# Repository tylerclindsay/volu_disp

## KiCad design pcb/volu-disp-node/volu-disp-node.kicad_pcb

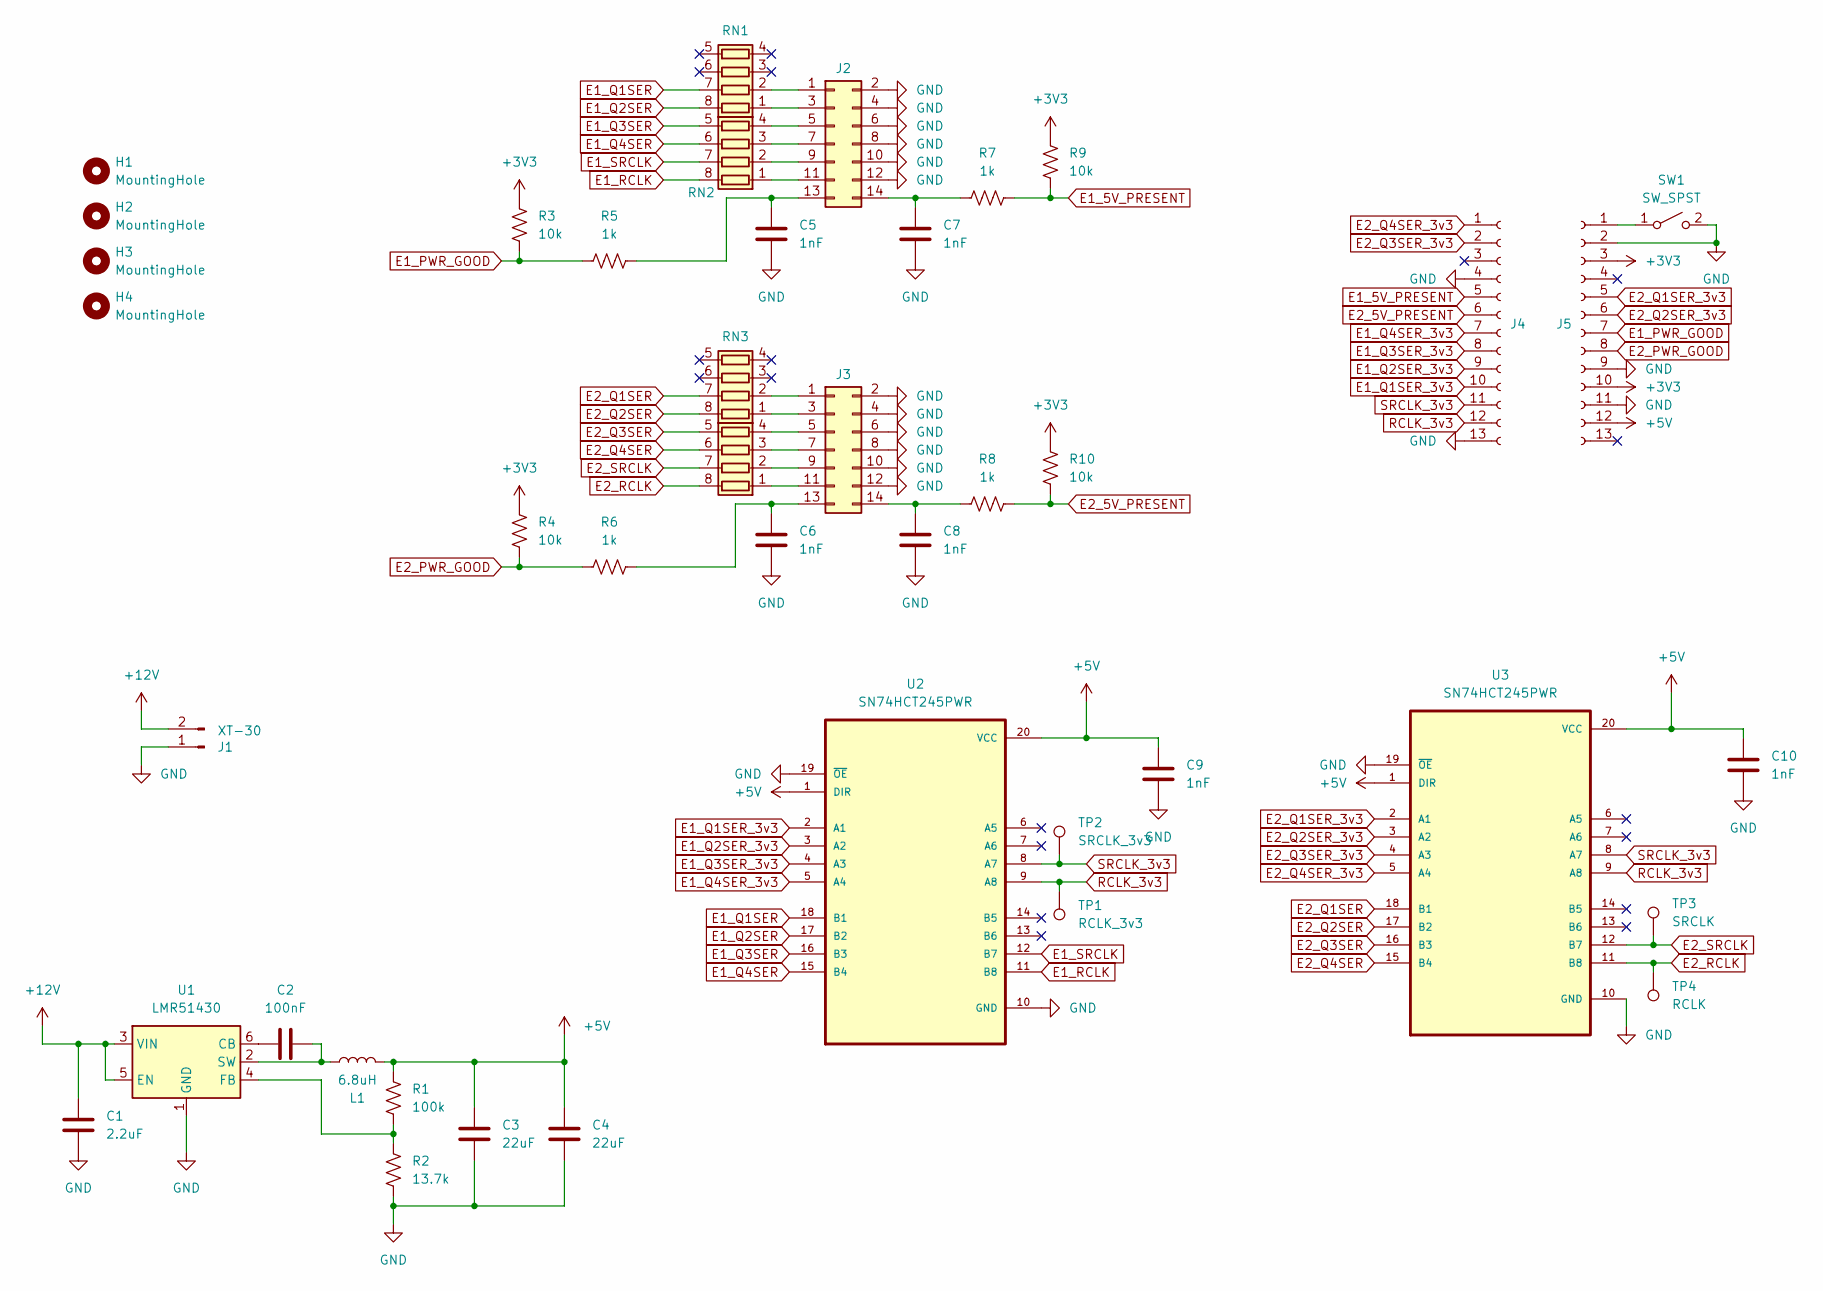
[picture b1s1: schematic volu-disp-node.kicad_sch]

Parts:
C1: 2.2uF; C_0603_1608Metric
C2: 100nF; C_0603_1608Metric
C3, C4: 22uF; C_0805_2012Metric
C5, C6, C7, C8, C9, C10: 1nF; C_0603_1608Metric
H1, H2, H3, H4: MountingHole; MountingHole_4.3mm_M4
J1: XT-30; AMASS_XT30PW-M_1x02_P2.50mm_Horizontal
J2, J3: Conn_02x07_Odd_Even; IDC-Header_2x07_P2.54mm_Latch_Vertical_SLIM
J4, J5: 01x13_Socket; PinSocket_1x13_P2.54mm_Vertical
L1: 6.8uH; L_7.3x7.3_H3.5
R1: 100k; R_0603_1608Metric
R2: 13.7k; R_0603_1608Metric
R3, R4, R9, R10: 10k; R_0603_1608Metric
R5, R6, R7, R8: 1k; R_0603_1608Metric
RN1, RN2, RN3, RN4: R_Pack04; R_Array_Convex_4x0603
SW1: SW_SPST; SW4_PTS815 SJM 250 SMTR LFS_CNK
TP1: RCLK_3v3; TestPoint_Pad_D2.0mm
TP2: SRCLK_3v3; TestPoint_Pad_D2.0mm
TP3: SRCLK; TestPoint_Pad_D2.0mm
TP4: RCLK; TestPoint_Pad_D2.0mm
U1: LMR51430; SOT-23-6
U2, U3: SN74HCT245PWR; SOP65P640X120-20N

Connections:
+3V3: J5.3, J5.10, R3.1, R4.1, R9.1, R10.1
+5V: C3.1, C4.1, C9.1, C10.1, J5.12, L1.2, R1.1, U2.1 (DIR), U2.20 (VCC), U3.1 (DIR), U3.20 (VCC)
+12V: C1.1, J1.2, U1.3 (VIN), U1.5 (EN)
E1_5V_PRESENT: J4.5, R7.2, R9.2
E1_PWR_GOOD: J5.7, R3.2, R5.1
E1_Q1SER: RN1.7 (R2.2), U2.18 (B1)
E1_Q1SER_3v3: J4.10, U2.2 (A1)
E1_Q2SER: RN1.8 (R1.2), U2.17 (B2)
E1_Q2SER_3v3: J4.9, U2.3 (A2)
E1_Q3SER: RN2.5 (R4.2), U2.16 (B3)
E1_Q3SER_3v3: J4.8, U2.4 (A3)
E1_Q4SER: RN2.6 (R3.2), U2.15 (B4)
E1_Q4SER_3v3: J4.7, U2.5 (A4)
E1_RCLK: RN2.8 (R1.2), U2.11 (B8)
E1_SRCLK: RN2.7 (R2.2), U2.12 (B7)
E2_5V_PRESENT: J4.6, R8.2, R10.2
E2_PWR_GOOD: J5.8, R4.2, R6.1
E2_Q1SER: RN3.7 (R2.2), U3.18 (B1)
E2_Q1SER_3v3: J5.5, U3.2 (A1)
E2_Q2SER: RN3.8 (R1.2), U3.17 (B2)
E2_Q2SER_3v3: J5.6, U3.3 (A2)
E2_Q3SER: RN4.5 (R4.2), U3.16 (B3)
E2_Q3SER_3v3: J4.2, U3.4 (A3)
E2_Q4SER: RN4.6 (R3.2), U3.15 (B4)
E2_Q4SER_3v3: J4.1, U3.5 (A4)
E2_RCLK: RN4.8 (R1.2), TP4.1, U3.11 (B8); also elsewhere on the board
E2_SRCLK: RN4.7 (R2.2), TP3.1, U3.12 (B7); also elsewhere on the board
GND: C1.2, C3.2, C4.2, C5.2, C6.2, C7.2, C8.2, C9.2, C10.2, J1.1, J2.2, J2.4, J2.6, J2.8, J2.10, J2.12, J3.2, J3.4, J3.6, J3.8, J3.10, J3.12, J4.4, J4.13, J5.2, J5.9, J5.11, R2.2, SW1.2 (B), U1.1 (GND), U2.10 (GND), U2.19 (~OE), U3.10 (GND), U3.19 (~OE)
unnamed: J2.1, RN1.2 (R2.1)
unnamed: J2.3, RN1.1 (R1.1)
unnamed: J2.5, RN2.4 (R4.1)
unnamed: J2.7, RN2.3 (R3.1)
unnamed: J2.9, RN2.2 (R2.1)
unnamed: J2.11, RN2.1 (R1.1)
unnamed: C5.1, J2.13, R5.2
unnamed: C7.1, J2.14, R7.1
unnamed: J3.1, RN3.2 (R2.1)
unnamed: J3.3, RN3.1 (R1.1)
unnamed: J3.5, RN4.4 (R4.1)
unnamed: J3.7, RN4.3 (R3.1)
unnamed: J3.9, RN4.2 (R2.1)
unnamed: J3.11, RN4.1 (R1.1)
unnamed: C6.1, J3.13, R6.2
unnamed: C8.1, J3.14, R8.1
unnamed: J5.1, SW1.1 (A)
unnamed: C2.1, U1.6 (CB)
unnamed: R1.2, R2.1, U1.4 (FB)
unnamed: C2.2, L1.1, U1.2 (SW)
RCLK_3v3: J4.12, TP1.1, U2.9 (A8), U3.9 (A8); also elsewhere on the board
SRCLK_3v3: J4.11, TP2.1, U2.8 (A7), U3.8 (A7); also elsewhere on the board

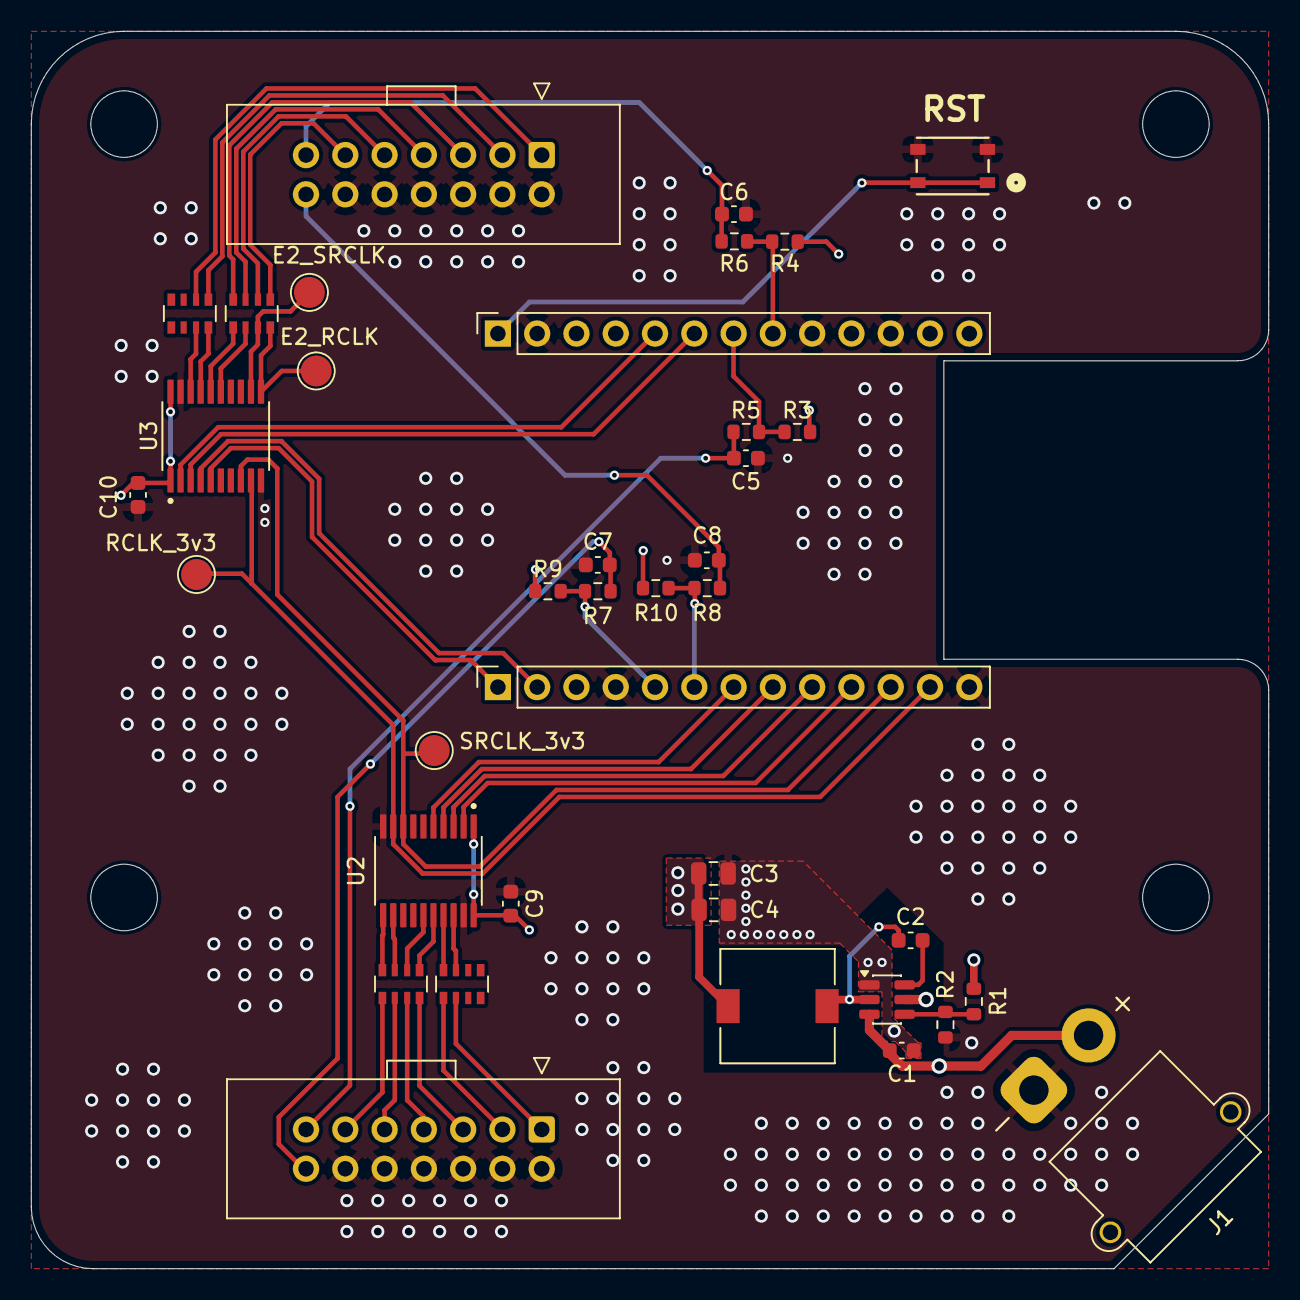
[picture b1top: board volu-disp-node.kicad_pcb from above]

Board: 4 copper layers, 80.0 x 80.0 mm, 42 parts (0 on the bottom side), 50 nets.

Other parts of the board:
E2_RCLK: RCLK; TestPoint_Pad_D2.0mm
E2_SRCLK: SRCLK; TestPoint_Pad_D2.0mm
RCLK_3v3: RCLK_3v3; TestPoint_Pad_D2.0mm
SRCLK_3v3: SRCLK_3v3; TestPoint_Pad_D2.0mm

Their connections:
E2_RCLK: E2_RCLK.1; also elsewhere on the board
E2_SRCLK: E2_SRCLK.1; also elsewhere on the board
RCLK_3v3: RCLK_3v3.1; also elsewhere on the board
SRCLK_3v3: SRCLK_3v3.1; also elsewhere on the board

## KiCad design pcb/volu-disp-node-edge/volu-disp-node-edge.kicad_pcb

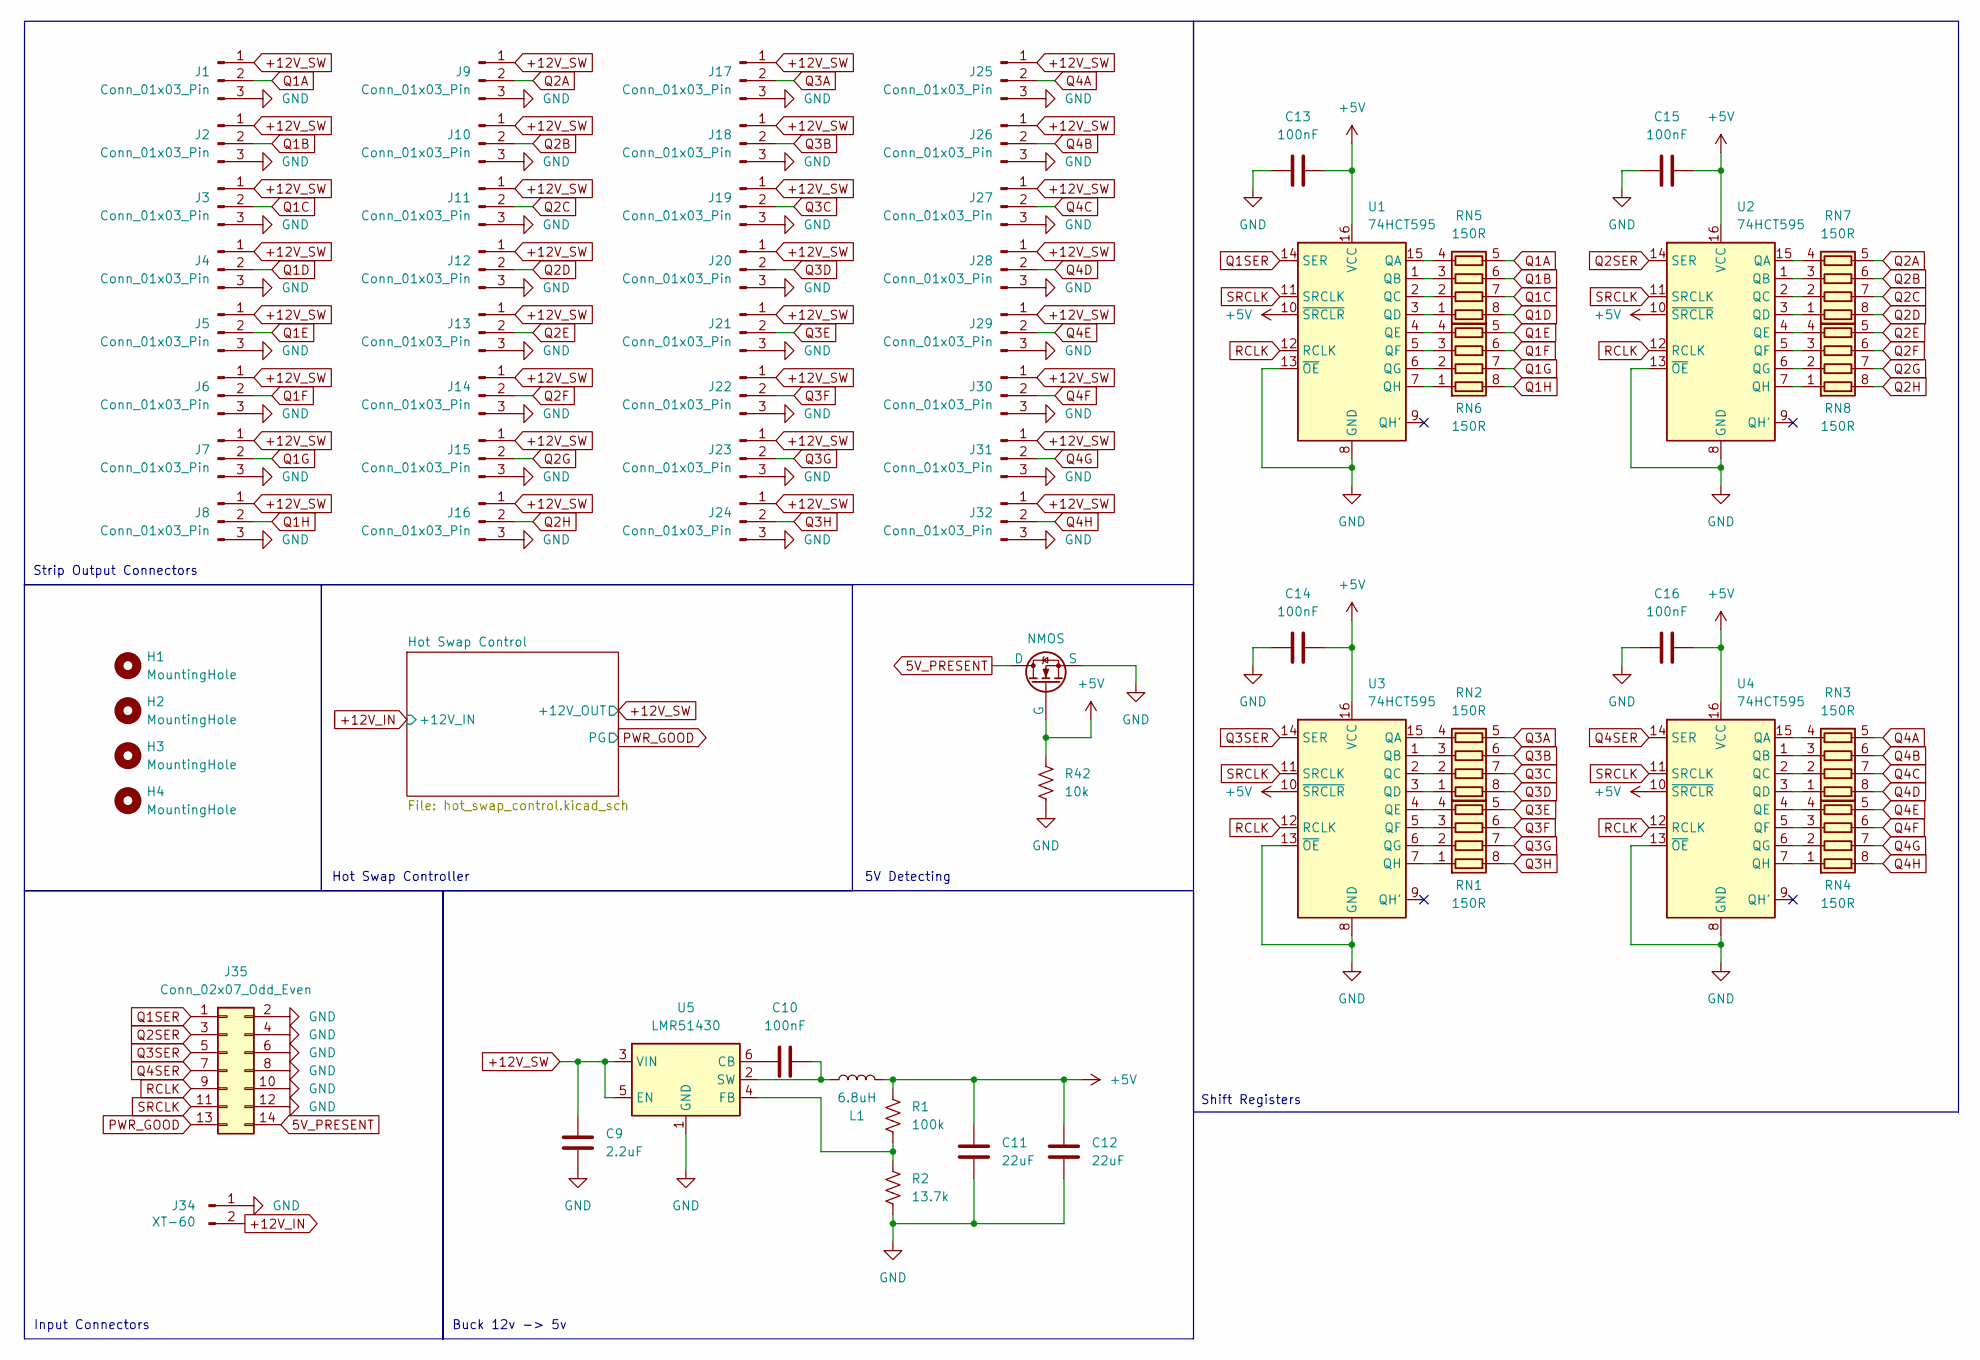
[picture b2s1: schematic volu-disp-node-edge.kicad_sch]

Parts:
C9: 2.2uF; C_0603_1608Metric
C10, C13, C14, C15, C16: 100nF; C_0603_1608Metric
C11, C12: 22uF; C_0805_2012Metric
H1, H2, H3, H4: MountingHole; MountingHole_4.3mm_M4
J1, J2, J3, J4, J5, J6, J7, J8, J9, J10, J11, J12, J13, J14, J15, J16, J17, J18, J19, J20, J21, J22, J23, J24, J25, J26, J27, J28, J29, J30, J31, J32: Conn_01x03_Pin; JST_XH_B3B-XH-A_1x03_P2.50mm_Vertical
J34: XT-60; AMASS_XT60PW-M_1x02_P7.20mm_Horizontal
J35: Conn_02x07_Odd_Even; IDC-Header_2x07_P2.54mm_Latch_Vertical
L1: 6.8uH; L_7.3x7.3_H3.5
Q2: NMOS; SOT-23
R1: 100k; R_0603_1608Metric
R2: 13.7k; R_0603_1608Metric
R42: 10k; R_0603_1608Metric
RN1, RN2, RN3, RN4, RN5, RN6, RN7, RN8: 150R; R_Array_Convex_4x0603
U1, U2, U3, U4: 74HCT595; SOIC-16_3.9x9.9mm_P1.27mm
U5: LMR51430; SOT-23-6

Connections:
5V_PRESENT: J35.14, Q2.3 (D)
+5V: C11.1, C12.1, C13.2, C14.2, C15.2, C16.2, L1.2, Q2.1 (G), R1.1, R42.1, U1.10 (~SRCLR), U1.16 (VCC), U2.10 (~SRCLR), U2.16 (VCC), U3.10 (~SRCLR), U3.16 (VCC), U4.10 (~SRCLR), U4.16 (VCC)
+12V_IN: J34.2; also elsewhere on the board
+12V_SW: C9.1, J1.1, J2.1, J3.1, J4.1, J5.1, J6.1, J7.1, J8.1, J9.1, J10.1, J11.1, J12.1, J13.1, J14.1, J15.1, J16.1, J17.1, J18.1, J19.1, J20.1, J21.1, J22.1, J23.1, J24.1, J25.1, J26.1, J27.1, J28.1, J29.1, J30.1, J31.1, J32.1, U5.3 (VIN), U5.5 (EN); also elsewhere on the board
GND: C9.2, C11.2, C12.2, C13.1, C14.1, C15.1, C16.1, J1.3, J2.3, J3.3, J4.3, J5.3, J6.3, J7.3, J8.3, J9.3, J10.3, J11.3, J12.3, J13.3, J14.3, J15.3, J16.3, J17.3, J18.3, J19.3, J20.3, J21.3, J22.3, J23.3, J24.3, J25.3, J26.3, J27.3, J28.3, J29.3, J30.3, J31.3, J32.3, J34.1, J35.2, J35.4, J35.6, J35.8, J35.10, J35.12, Q2.2 (S), R2.2, R42.2, U1.8 (GND), U1.13 (~OE), U2.8 (GND), U2.13 (~OE), U3.8 (GND), U3.13 (~OE), U4.8 (GND), U4.13 (~OE), U5.1 (GND); also elsewhere on the board
unnamed: RN1.1 (R1.1), U3.7 (QH)
unnamed: RN1.2 (R2.1), U3.6 (QG)
unnamed: RN1.3 (R3.1), U3.5 (QF)
unnamed: RN1.4 (R4.1), U3.4 (QE)
unnamed: RN2.1 (R1.1), U3.3 (QD)
unnamed: RN2.2 (R2.1), U3.2 (QC)
unnamed: RN2.3 (R3.1), U3.1 (QB)
unnamed: RN2.4 (R4.1), U3.15 (QA)
unnamed: RN3.1 (R1.1), U4.3 (QD)
unnamed: RN3.2 (R2.1), U4.2 (QC)
unnamed: RN3.3 (R3.1), U4.1 (QB)
unnamed: RN3.4 (R4.1), U4.15 (QA)
unnamed: RN4.1 (R1.1), U4.7 (QH)
unnamed: RN4.2 (R2.1), U4.6 (QG)
unnamed: RN4.3 (R3.1), U4.5 (QF)
unnamed: RN4.4 (R4.1), U4.4 (QE)
unnamed: RN5.1 (R1.1), U1.3 (QD)
unnamed: RN5.2 (R2.1), U1.2 (QC)
unnamed: RN5.3 (R3.1), U1.1 (QB)
unnamed: RN5.4 (R4.1), U1.15 (QA)
unnamed: RN6.1 (R1.1), U1.7 (QH)
unnamed: RN6.2 (R2.1), U1.6 (QG)
unnamed: RN6.3 (R3.1), U1.5 (QF)
unnamed: RN6.4 (R4.1), U1.4 (QE)
unnamed: RN7.1 (R1.1), U2.3 (QD)
unnamed: RN7.2 (R2.1), U2.2 (QC)
unnamed: RN7.3 (R3.1), U2.1 (QB)
unnamed: RN7.4 (R4.1), U2.15 (QA)
unnamed: RN8.1 (R1.1), U2.7 (QH)
unnamed: RN8.2 (R2.1), U2.6 (QG)
unnamed: RN8.3 (R3.1), U2.5 (QF)
unnamed: RN8.4 (R4.1), U2.4 (QE)
unnamed: C10.1, U5.6 (CB)
unnamed: R1.2, R2.1, U5.4 (FB)
unnamed: C10.2, L1.1, U5.2 (SW)
PWR_GOOD: J35.13; also elsewhere on the board
Q1A: J1.2, RN5.5 (R4.2)
Q1B: J2.2, RN5.6 (R3.2)
Q1C: J3.2, RN5.7 (R2.2)
Q1D: J4.2, RN5.8 (R1.2)
Q1E: J5.2, RN6.5 (R4.2)
Q1F: J6.2, RN6.6 (R3.2)
Q1G: J7.2, RN6.7 (R2.2)
Q1H: J8.2, RN6.8 (R1.2)
Q1SER: J35.1, U1.14 (SER)
Q2A: J9.2, RN7.5 (R4.2)
Q2B: J10.2, RN7.6 (R3.2)
Q2C: J11.2, RN7.7 (R2.2)
Q2D: J12.2, RN7.8 (R1.2)
Q2E: J13.2, RN8.5 (R4.2)
Q2F: J14.2, RN8.6 (R3.2)
Q2G: J15.2, RN8.7 (R2.2)
Q2H: J16.2, RN8.8 (R1.2)
Q2SER: J35.3, U2.14 (SER)
Q3A: J17.2, RN2.5 (R4.2)
Q3B: J18.2, RN2.6 (R3.2)
Q3C: J19.2, RN2.7 (R2.2)
Q3D: J20.2, RN2.8 (R1.2)
Q3E: J21.2, RN1.5 (R4.2)
Q3F: J22.2, RN1.6 (R3.2)
Q3G: J23.2, RN1.7 (R2.2)
Q3H: J24.2, RN1.8 (R1.2)
Q3SER: J35.5, U3.14 (SER)
Q4A: J25.2, RN3.5 (R4.2)
Q4B: J26.2, RN3.6 (R3.2)
Q4C: J27.2, RN3.7 (R2.2)
Q4D: J28.2, RN3.8 (R1.2)
Q4E: J29.2, RN4.5 (R4.2)
Q4F: J30.2, RN4.6 (R3.2)
Q4G: J31.2, RN4.7 (R2.2)
Q4H: J32.2, RN4.8 (R1.2)
Q4SER: J35.7, U4.14 (SER)
RCLK: J35.9, U1.12 (RCLK), U2.12 (RCLK), U3.12 (RCLK), U4.12 (RCLK)
SRCLK: J35.11, U1.11 (SRCLK), U2.11 (SRCLK), U3.11 (SRCLK), U4.11 (SRCLK)

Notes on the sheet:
Buck 12v -> 5v
Strip Output Connectors
5V Detecting
Hot Swap Controller
Input Connectors
Shift Registers

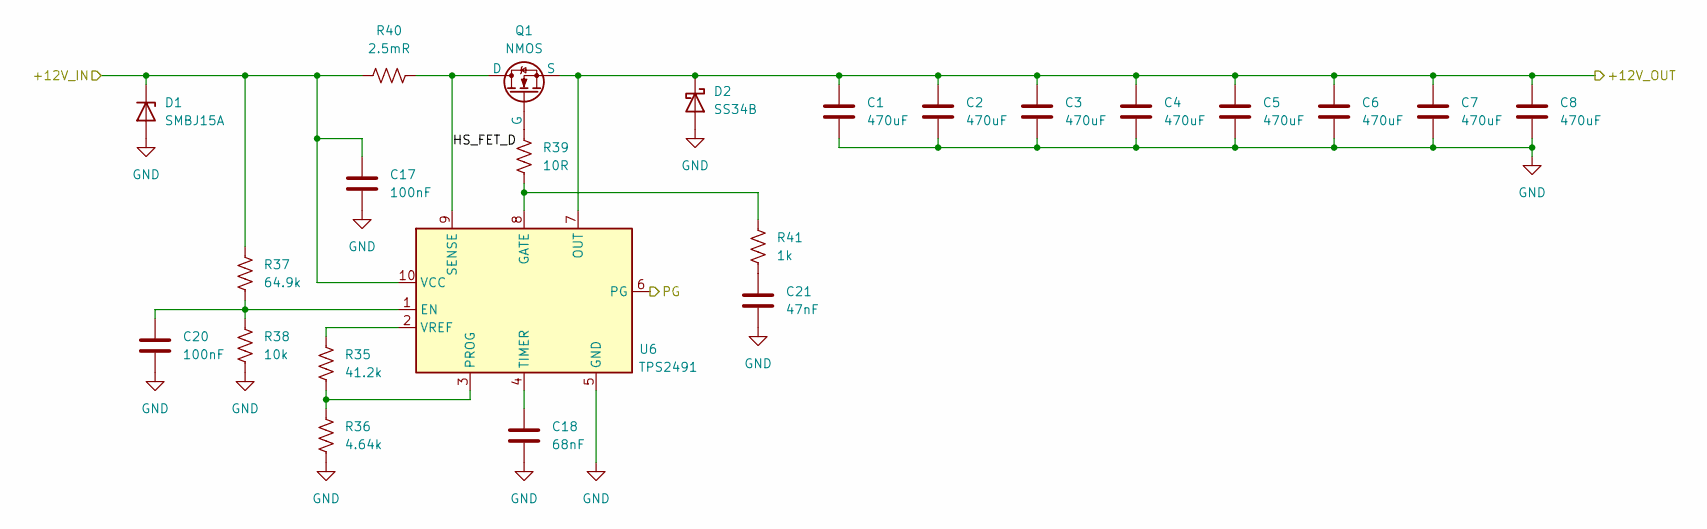
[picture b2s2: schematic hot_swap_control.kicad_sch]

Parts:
C1, C2, C3, C4, C5, C6, C7, C8: 470uF; CP_Radial_D10.0mm_P5.00mm
C17, C20: 100nF; C_0603_1608Metric
C18: 68nF; C_0603_1608Metric
C21: 47nF; C_0603_1608Metric
D1: SMBJ15A; D_SMB
D2: SS34B; D_SMB
Q1: NMOS; PQFN-8-EP_6x5mm_P1.27mm_Generic
R35: 41.2k; R_0603_1608Metric
R36: 4.64k; R_0603_1608Metric
R37: 64.9k; R_0603_1608Metric
R38: 10k; R_0603_1608Metric
R39: 10R; R_0603_1608Metric
R40: 2.5mR; R_2512_6332Metric
R41: 1k; R_0603_1608Metric
U6: TPS2491; VSSOP-10_3x3mm_P0.5mm

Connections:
+12V_IN: C17.1, D1.1 (K), R37.1, R40.1, U6.10 (VCC); also elsewhere on the board
+12V_SW: C1.1, C2.1, C3.1, C4.1, C5.1, C6.1, C7.1, C8.1, D2.1 (K), Q1.3 (S), U6.7 (OUT); also elsewhere on the board
/Hot Swap Control/HS_FET_D: Q1.1 (D), R40.2, U6.9 (SENSE)
GND: C1.2, C2.2, C3.2, C4.2, C5.2, C6.2, C7.2, C8.2, C17.2, C18.2, C20.2, C21.2, D1.2 (A), D2.2 (A), R36.2, R38.2, U6.5 (GND); also elsewhere on the board
unnamed: C21.1, R41.2
unnamed: Q1.2 (G), R39.1
unnamed: C20.1, R37.2, R38.1, U6.1 (EN)
unnamed: R39.2, R41.1, U6.8 (GATE)
unnamed: R35.2, R36.1, U6.3 (PROG)
unnamed: C18.1, U6.4 (TIMER)
unnamed: R35.1, U6.2 (VREF)
PWR_GOOD: U6.6 (PG); also elsewhere on the board

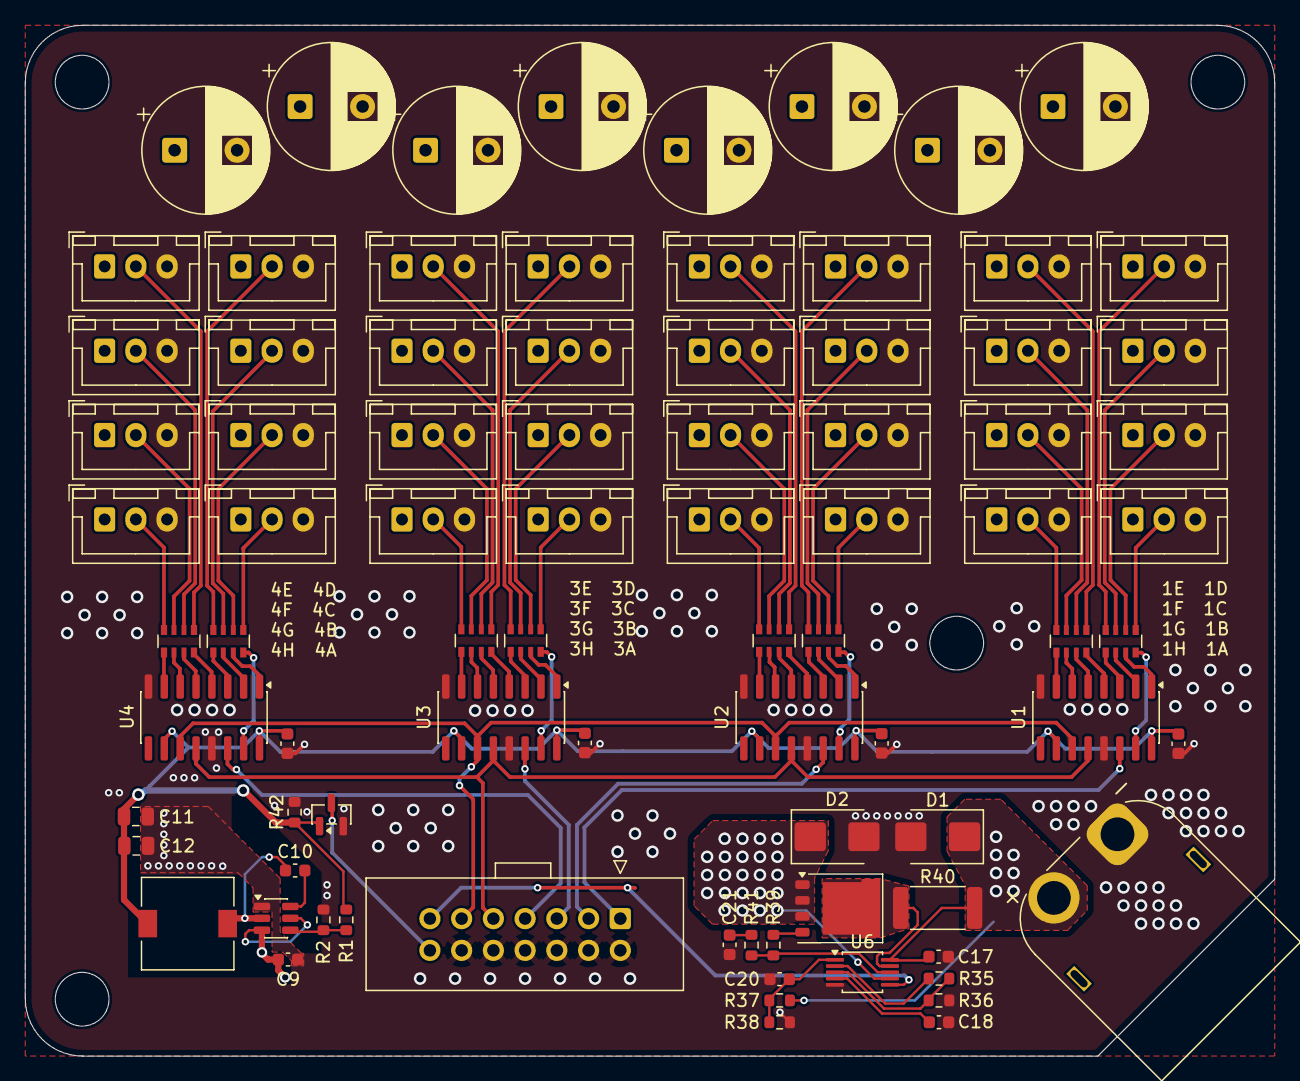
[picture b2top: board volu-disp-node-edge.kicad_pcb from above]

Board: 4 copper layers, 100.0 x 82.5 mm, 87 parts (0 on the bottom side), 87 nets.

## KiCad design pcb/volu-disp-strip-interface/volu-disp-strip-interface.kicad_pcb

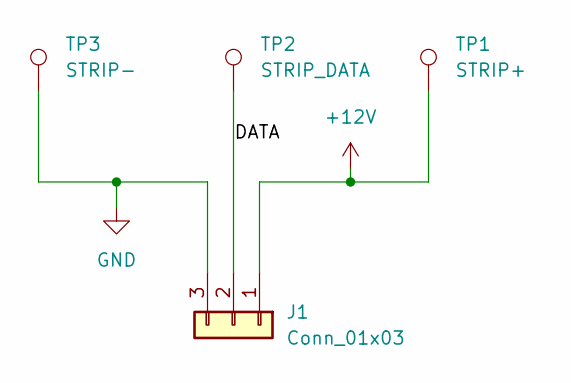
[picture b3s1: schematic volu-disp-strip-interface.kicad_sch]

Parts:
J1: Conn_01x03; JST_XH_B3B-XH-A_1x03_P2.50mm_Vertical
TP1: STRIP+; TestPoint_Pad_5.0x2mm_slim
TP2: STRIP_DATA; TestPoint_Pad_5.0x2mm_slim
TP3: STRIP-; TestPoint_Pad_5.0x2mm_slim

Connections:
+12V: J1.1, TP1.1
/DATA: J1.2, TP2.1
GND: J1.3, TP3.1

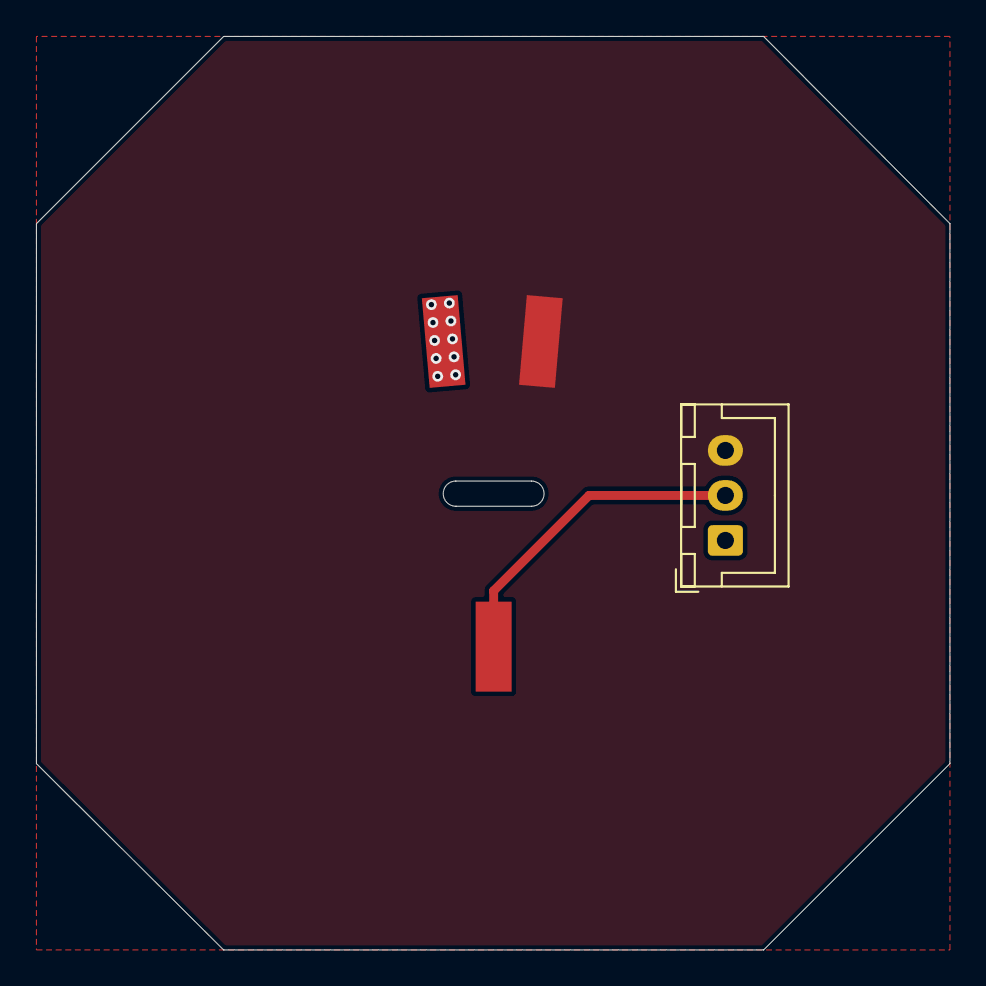
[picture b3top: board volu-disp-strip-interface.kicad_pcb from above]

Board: 2 copper layers, 50.8 x 50.8 mm, 4 parts (0 on the bottom side), 3 nets.

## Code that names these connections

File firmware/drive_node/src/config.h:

#pragma once
#include <Arduino.h>
#include <stdint.h>
// =============================================================================
//  config.h - WT32-ETH01 drive node, wire protocol v2, edge node output
// =============================================================================
//
//  Spec: docs/protocol.md. Summary (all multi-byte fields little-endian):
//
//  Common header (8 bytes)
//    0  1  magic    0xA7
//    1  1  version  2
//    2  1  type     1 PIXELS, 2 SYNC, 3 reserved (status); others ignored
//    3  1  flags    bit0 SHOW_NOW (PIXELS only); other bits must be 0
//    4  4  frame    u32 host frame sequence number
//
//  PIXELS (type 1): + offset u16, count u16 (1..486), then R,G,B x count.
//    Writes into the node's flat back buffer: pixel p of strip s is at
//    s * LEDS_PER_STRIP + p (pixel 0 = top of the strip). Packets may span
//    strips; pixels past the buffer end are ignored.
//  SYNC (type 2): header only, broadcast. Latch: back -> front, show.
//
//  PIXELS 1..8 frames older than the newest frame seen are late and dropped.
//
// =============================================================================

// ---------------------------------------------------------------------------
//  Node identity (override per node with -DNODE_ID=2 in platformio.ini)
// ---------------------------------------------------------------------------
#ifndef NODE_ID
#define NODE_ID 1
#endif

#define STR_(x) #x
#define STR(x)  STR_(x)
#define HOSTNAME "volu-disp-node-" STR(NODE_ID)

// ---------------------------------------------------------------------------
//  Strip layout (override per node with -DNUM_STRIPS=40 etc. in platformio.ini)
// ---------------------------------------------------------------------------
// Must match this node's section in config/displays/*.yaml:
//   NUM_STRIPS = section width * depth, LEDS_PER_STRIP = section height.
// Strip s is (z - z0) * width + (x - x0) (docs/hardware.md -> Drive node
// mapping) and plugs into edge node s / 32 (E1, E2), connector J(s % 32 + 1).
// Defaults: 40 x 12, matching config/displays/bench.yaml and each node of
// config/displays/prototype.yaml.
#ifndef NUM_STRIPS
#define NUM_STRIPS 40
#endif
#ifndef LEDS_PER_STRIP
#define LEDS_PER_STRIP 12
#endif

// ---------------------------------------------------------------------------
//  LED output: I2S1 -> 74HCT245 -> IDC -> edge node 74HCT595s
//  (src/edge_out.cpp, docs/decisions/0014-edge-node-output.md)
// ---------------------------------------------------------------------------
// Serial data line of each shift register: E<edge>_Q<register>SER.
// Register n of an edge node drives connectors J(8n-7)..J(8n) (outputs A..H).
#define PIN_E1_Q1SER 5    // strapping pin (SDIO timing only)
#define PIN_E1_Q2SER 12
#define PIN_E1_Q3SER 14
#define PIN_E1_Q4SER 15
#define PIN_E2_Q1SER 33
#define PIN_E2_Q2SER 32
#define PIN_E2_Q3SER 3    // UART0 RX: serial is off once the output starts
#define PIN_E2_Q4SER 1    // UART0 TX
#define PIN_SRCLK    4    // shift clock, shared by all 8 registers
#define PIN_RCLK     2    // latch clock, shared (strapping pin)

// Edge node power status inputs (pulled up on the drive node). 39, 36 and
// 35 are input-only pins; 17 is a normal GPIO.
#define PIN_E1_5V_PRESENT 39   // low = the edge node's 5V (595 supply) is up
#define PIN_E2_5V_PRESENT 36
#define PIN_E1_PWR_GOOD   17   // low = the edge node's 12V hot-swap is good
#define PIN_E2_PWR_GOOD   35   //   (reads high, not good, when unplugged)

// Only drive the data lines of edge nodes whose 5V is present (keeps logic
// levels off an unpowered 595). 0 = always drive both.
#define EDGE_POWER_CHECK 1
// How often the power inputs are read, ms.
#define EDGE_POWER_POLL_MS 50

// Sample clock = SRCLK = 80 MHz / I2S_CLK_DIV. 4 -> 20 MHz: a WS2811 bit is
// 3 slots x 8 samples = 1.2 us (T0H 0.4 us, T1H 0.8 us), 28.8 us per pixel.
#define I2S_CLK_DIV 4
// SRCLK polarity: 1 = rising edge mid-sample, as esp_lcd drives the I2S
// LCD write clock. Flip if a scope shows SER changing on the rising edge.
#define SRCLK_INVERT 1
// Lines held low (latch-only slots) after each frame, so the WS2811s latch:
// >= 50 us (datasheet; decision 0013's show-time model assumes 50). Rounds
// up to whole DMA buffers of 57.6 us.
#define LED_RESET_US 50
// LED byte order on the wire, as indices into the protocol's R,G,B. WS2811
// strips here are GRB.
#define LED_COLOR_ORDER 1, 0, 2

// Global brightness, 0-255 (255 = unchanged). The host applies brightness;
// keep this at 255 except for bench tests.
#define GLOBAL_BRIGHTNESS 255

// Blank all strips if no valid packet arrives for this many ms. 0 = never.
#define DATA_TIMEOUT_MS 3000

// ---------------------------------------------------------------------------
//  Network
// ---------------------------------------------------------------------------
#define UDP_PORT 7777

// Static IP: 192.168.1.(100 + NODE_ID)
#define NET_IP      192, 168, 1, (100 + NODE_ID)
#define NET_GATEWAY 192, 168, 1, 1
#define NET_MASK    255, 255, 255, 0

// WT32-ETH01 Ethernet PHY (LAN8720) - don't change for this board
#define ETH_PHY_TYPE_CFG  ETH_PHY_LAN8720
#define ETH_PHY_ADDR_CFG  1
#define ETH_PHY_MDC_CFG   23
#define ETH_PHY_MDIO_CFG  18
#define ETH_PHY_POWER_CFG 16
#define ETH_CLK_MODE_CFG  ETH_CLOCK_GPIO0_IN

// ---------------------------------------------------------------------------
//  OTA
// ---------------------------------------------------------------------------
#define OTA_ENABLED  1
// OTA_PASSWORD is injected via build_flags from secrets.ini (gitignored)
#ifndef OTA_PASSWORD
#error "OTA_PASSWORD not defined - copy secrets.ini.example to secrets.ini"
#endif

// ---------------------------------------------------------------------------
//  Protocol v2 (must match docs/protocol.md and volu_gen/output/protocol.py)
// ---------------------------------------------------------------------------
#define PROTO_MAGIC        0xA7
#define PROTO_VERSION      2
#define TYPE_PIXELS        1
#define TYPE_SYNC          2
#define FLAG_SHOW_NOW      0x01
#define HEADER_SIZE        8
#define PIXELS_HEADER_SIZE 12
#define MAX_PACKET_SIZE    1472   // fits a standard 1500 byte MTU
#define MAX_PIXELS_PER_PACKET ((MAX_PACKET_SIZE - PIXELS_HEADER_SIZE) / 3)  // 486
#define LATE_WINDOW        8      // PIXELS 1..8 frames old are dropped

// ---------------------------------------------------------------------------
//  Tasks / debug
// ---------------------------------------------------------------------------
// Max packets processed per loop pass, so a flood can't starve OTA.
#define MAX_PACKETS_PER_LOOP 64

// The show task (front buffer -> LEDs) runs on the same core as loop(), at
// a higher priority: it copies and starts each show, then blocks while the
// LEDs clock out, so receiving continues during the show.
#define SHOW_TASK_CORE     1
#define SHOW_TASK_PRIORITY 2
#define SHOW_TASK_STACK    4096

// Report packet/frame stats every N ms. 0 = off.
#define STATS_INTERVAL_MS 5000

// UART0's pins (IO1, IO3) carry E2 Q4/Q3 data, so serial output stops when
// the LED output starts (after the boot banner). Stats and status messages
// go as text over UDP to this port on the host that last sent a valid
// packet (listen with tools/node_stats.py). 0 = off.
#define STATS_UDP_PORT 7778

// Bench/debug only: 1 keeps serial on IO1/IO3 and leaves E2 Q3/Q4 (strips
// 48-63) undriven; stats also go to serial. Can be set with -DKEEP_SERIAL=1.
#ifndef KEEP_SERIAL
#define KEEP_SERIAL 0
#endif
